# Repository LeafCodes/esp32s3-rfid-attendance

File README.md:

# 📇 ESP32-S3 RFID Attendance System

> **Sistem Presensi RFID Mandiri Berbasis IoT & Local-First Architecture**  
> Solusi presensi cerdas, hemat biaya, dan tahan kendala jaringan dengan integrasi *end-to-end*: **Custom PCB (KiCad) + Embedded C++ (ESP32-S3) + Modern Web Backend (FastAPI & SQLite)**.

---

## 📌 Latar Belakang & Masalah (*Problem Statement*)

Banyak institusi, sekolah, laboratorium, maupun startup menghadapi berbagai kendala dalam pencatatan kehadiran:
1. **Absensi Manual / Kertas**: Rawan manipulasi, rawan hilang, dan memakan waktu rekapitulasi yang tinggi.
2. **Mesin Biometrik (Fingerprint) Konvensional**: Sering gagal mengenali sidik jari yang kotor, berminyak, atau basah; menimbulkan antrean panjang di jam sibuk kerja/sekolah.
3. **Sistem Cloud Murni (*Pure Cloud-Dependent*)**: Jika koneksi internet ISP luar mati (*down*) atau latensi tinggi, seluruh proses absensi di kantor menjadi lumpuh dan karyawan tidak bisa tap kartu.
4. **Konfigurasi Jaringan yang Rumit**: Perangkat IoT tradisional sering mengharuskan pengaturan IP statis (*hardcoded*) pada firmware setiap kali berpindah router/jaringan.

---

## 💡 Solusi yang Ditawarkan (*The Engineering Solution*)

Proyek ini menghadirkan **arsitektur presensi lokal-mandiri (*Local-First & Offline-Resilient*)** yang andal dan mudah dioperasikan tanpa ketergantungan pada internet publik:

- 🛡️ **Offline-First & Auto-Synchronization**:  
  ESP32-S3 menyimpan daftar UID kartu aktif di memori EEPROM/Flash. Jika server PC atau jaringan mati, proses *tap* tetap berhasil dicatat ke dalam memori *offline buffer* lokal (LittleFS/RAM). Begitu server kembali online, data transaksi otomatis terkirim tanpa ada absensi yang hilang.
- 🔍 **Zero-Configuration Network (mDNS Discovery)**:  
  ESP32 secara cerdas mencari keberadaan server PC lokal di jaringan menggunakan protokol mDNS (`absensi-pc.local`). Pengguna tidak perlu mengubah kode atau mengatur IP statis saat berganti router.
- 📶 **WiFi Captive Portal (WiFiManager)**:  
  Konfigurasi SSID dan password dilakukan melalui halaman *web portal* saat ESP32 pertama kali dinyalakan atau saat jaringan berubah, tanpa perlu *flash* ulang firmware.
- ⏱️ **Double-Tap Debounce Protection**:  
  Backend FastAPI dilengkapi proteksi logika selisih waktu (<10 detik) untuk mencegah terjadinya duplikasi data saat karyawan menempelkan kartu berulang kali tanpa sengaja.
- 🔊 **Feedback Visual & Audio Real-Time**:  
  Respon instan kepada pengguna melalui LCD 16x2 I2C (nama karyawan dan status Masuk/Pulang), lampu status Dual LED, dan nada Buzzer spesifik (sukses vs ditolak).
- 📊 **Dashboard Interaktif & One-Click Excel Export**:  
  Admin dapat memantau log kehadiran secara *real-time*, mendaftarkan kartu baru via browser, dan mengekspor laporan lengkap ke format Microsoft Excel (`.xlsx`) siap olah.
- 🛠️ **Full-Stack Hardware-to-Software**:  
  Dirancang dari level sirkuit elektronik (desain skematik & PCB di KiCad), enclosure 3D print, hingga *full-stack software*.

---

## 🏗️ Arsitektur Sistem

Berikut adalah gambaran interaksi antara komponen perangkat keras dan aplikasi server:

```mermaid
flowchart LR
    subgraph EdgeDevice[" Perangkat Keras (Edge Device) "]
        RFID["RFID MFRC522\n(13.56MHz SPI)"] --> ESP["ESP32-S3 MCU\n(Dual-Core Xtensa)"]
        ESP --> LCD["LCD 16x2 I2C\n(Visual Info)"]
        ESP --> BUZZ["Buzzer & LED\n(Audio-Visual Status)"]
        ESP -. Buffer Luring .-> FS["Internal Flash / EEPROM\n(Offline Buffer & Card DB)"]
    end

    subgraph LocalNetwork[" Jaringan Area Lokal (WiFi / LAN) "]
        ESP -- "mDNS Service Discovery" --- MDNS["Resolusi: absensi-pc.local"]
        ESP -- "REST API (JSON / HTTP)" --- API["POST /api/attendance\nGET /api/cards"]
    end

    subgraph HostPC[" Server Lokal (PC / Mini PC) "]
        API --> FastAPI["FastAPI Backend Server\n(Uvicorn ASGI Engine)"]
        FastAPI --> SQLite[("SQLite Database\n(Cards, Logs, Settings)")]
        FastAPI --> WebUI["Web Dashboard & Reports\n(Jinja2 + Tailwind)"]
        FastAPI --> Excel["Export Engine\n(OpenPyXL .xlsx)"]
    end
```

> 📖 **Pelajari detail alur sistem & flowchart lengkap:** [docs/architecture_flowchart.md](docs/architecture_flowchart.md)

---

## ✨ Fitur-Fitur Utama

### 1. Sisi Firmware (ESP32-S3)
* **Dual-State Attendance Toggle**: Menentukan otomatis pergantian status `IN` (Masuk) atau `OUT` (Keluar).
* **NTP Clock Synchronization**: Jam internal tersinkronisasi otomatis via NTP (*Network Time Protocol*).
* **Smart Offline Buffer Recovery**: Mengirim antrean data luring secara otomatis begitu koneksi ke server pulih.
* **Modular Codebase**: Kode C++ tertata rapi dalam modul terpisah (`wifi_manager`, `rfid_handler`, `pc_client`, `offline_buffer`, `lcd_display`, `led_buzzer`).

### 2. Sisi Server & Web App (FastAPI)
* **Realtime Dashboard**: Menampilkan status kehadiran hari ini, waktu *tap*, serta rincian karyawan.
* **Interactive Enrollment Mode**: Pendaftaran kartu baru langsung dari web browser. Saat mode aktivasi menyala, kartu yang di-tap otomatis terdaftar ke profil pegawai baru.
* **Audit & Export Excel**: Unduh rekapitulasi presensi harian/bulanan dengan format rapi dan siap cetak.
* **Lightweight & High Performance**: Dibangun menggunakan FastAPI asynchronous dengan SQLite yang ringan dan mudah di-backup.

### 3. Sisi Hardware & PCB
* **Custom KiCad Design**: Skematik dan layout 2-layer siap cetak (*home-etching* toner transfer atau fabrikasi JLCPCB/PCBWay).
* **Decoupling Protection**: Dilengkapi kapasitor peredam *noise* pada jalur suplai daya MFRC522 dan ESP32.
* **Mounting Enclosure Ready**: Dimensi PCB 100×80 mm dirancang presisi untuk box/casing 3D print.

---

## 🧰 Kebutuhan Komponen (Hardware & Software)

### Komponen Elektronika
| Komponen | Spesifikasi / Tipe | Fungsi |
|---|---|---|
| **Microcontroller** | ESP32-S3 DevKitC-1 (WiFi + BLE) | Pemroses utama, konektivitas, buffer memori |
| **RFID Reader** | MFRC522 (13.56 MHz, SPI Interface) | Pembaca kartu RFID MIFARE |
| **Display** | LCD 16x2 Karakter dengan I2C Backpack | Penampil jam, sapaan nama, dan status |
| **Audio-Visual** | Active Buzzer 5V, LED Hijau, LED Merah | Indikator status sukses / ditolak |
| **Kartu/Tag** | MIFARE Classic 1K Card / Keyfob | Identitas pengguna / karyawan |
| **Catu Daya** | 5V DC (USB-C atau Adaptor 5V 1A) | Sumber daya sistem |

### Perangkat Lunak & Library
* **Firmware**: PlatformIO IDE, Arduino Framework for ESP32, LittleFS, ArduinoJson, MFRC522, LiquidCrystal_I2C, WiFiManager.
* **PC Backend**: Python 3.12+, FastAPI, Uvicorn, SQLAlchemy, SQLite, OpenPyXL, python-zeroconf.
* **EDA / PCB Tool**: KiCad 8.0+.

---

## 🚀 Panduan Memulai Cepat (*Quick Start*)

### 1. Flash Firmware ke ESP32-S3
Pastikan Anda telah memasang [PlatformIO Core / IDE](https://platformio.org/).

```bash
# Masuk ke direktori firmware
cd firmware

# Compile dan upload ke board ESP32-S3
pio run -t upload

# Buka Serial Monitor untuk memantau proses boot
pio device monitor
```

### 2. Menjalankan Server PC (FastAPI)
Buka terminal baru di komputer yang terhubung ke jaringan WiFi/LAN yang sama:

```bash
# Masuk ke direktori pc-app
cd pc-app

# Buat virtual environment (opsional namun disarankan)
python -m venv venv
# Windows:
venv\Scripts\activate
# Linux/macOS:
# source venv/bin/activate

# Install dependensi
pip install -r requirements.txt

# Jalankan server FastAPI
uvicorn app.main:app --host 0.0.0.0 --port 8000
```

### 3. Mengakses Web Dashboard
Buka browser web di komputer Anda lalu akses salah satu alamat berikut:
- 🌐 `http://localhost:8000`
- 🌐 `http://absensi-pc.local:8000`

---

## 📂 Struktur Repositori

```text
projek_absensi_rfid/
├── firmware/                  # Proyek Firmware PlatformIO (ESP32-S3)
│   ├── src/                   # Source code modular C++
│   │   ├── main.ino           # Logika utama (setup & loop)
│   │   ├── config.h           # Pemetaan pin hardware & parameter sistem
│   │   ├── rfid_handler.cpp   # Driver komunikasi MFRC522 (SPI)
│   │   ├── pc_client.cpp      # Klien HTTP REST API ke server PC
│   │   ├── mdns_client.cpp    # Resolusi nama server otomatis (mDNS)
│   │   ├── offline_buffer.cpp # Manajemen buffer antrean offline
│   │   ├── card_storage.cpp   # Cache UID kartu lokal pada Flash
│   │   └── ...
│   ├── include/               # Header deklarasi
│   └── platformio.ini         # Konfigurasi board & dependensi library
├── pc-app/                    # Aplikasi Server & Web (FastAPI)
│   ├── app/
│   │   ├── main.py            # Entry point FastAPI & zeroconf mDNS advertiser
│   │   ├── database.py        # Konfigurasi database SQLite & ORM engine
│   │   ├── models.py          # Model database: Card & AttendanceLog
│   │   ├── routes/            # REST API endpoints (cards, attendance, reports)
│   │   ├── services/          # Layanan mDNS broadcast & sync logic
│   │   ├── templates/         # UI Dashboard HTML (Jinja2)
│   │   └── static/            # Styling CSS & aset web
│   ├── tests/                 # Unit testing (Pytest)
│   └── requirements.txt       # Daftar dependensi Python
├── pcb/                       # Desain Perangkat Keras PCB (KiCad)
│   └── rfid-attendance/       # File skematik (.kicad_sch), PCB (.kicad_pcb),
│                              # dan berkas export SVG siap cetak
├── case/                      # File rancangan 3D enclosure / casing
├── docs/                      # Dokumentasi Teknis Mendalam
│   ├── architecture_flowchart.md # Diagram alur data & state machine lengkap
│   ├── setup-guide.md            # Panduan langkah demi langkah untuk teknisi & user
│   └── wiring.md                 # Diagram skematik pinout hardware & kelistrikan
└── README.md                  # Halaman utama dokumentasi proyek
```

---

## 📚 Panduan Dokumentasi Lengkap

Untuk eksplorasi teknis yang lebih komprehensif, silakan pelajari dokumen-dokumen berikut:
- 📐 [**Diagram Pengkabelan & Pinout (Wiring)**](docs/wiring.md) — Rincian jalur pin SPI/I2C/GPIO, level voltase, dan panduan kestabilan daya.
- ⚙️ [**Arsitektur & Flowchart Sistem**](docs/architecture_flowchart.md) — Alur logika state machine, penanganan offline buffer, dan kontrak API.
- 📖 [**Panduan Penggunaan & Troubleshooting**](docs/setup-guide.md) — Langkah operasional bagi pengguna non-teknis serta matriks penanganan masalah.
- 🔌 [**Dokumentasi Desain PCB & Fabrikasi**](pcb/rfid-attendance/README.md) — Spesifikasi PCB 2-layer, Bill of Materials (BOM), dan panduan cetak KiCad.

---

## 👨‍💻 Kontribusi & Lisensi

Proyek ini dirilis di bawah lisensi terbuka [MIT License](LICENSE). Bebas digunakan, dimodifikasi, dan dikembangkan untuk keperluan riset, edukasi, maupun implementasi komersial.

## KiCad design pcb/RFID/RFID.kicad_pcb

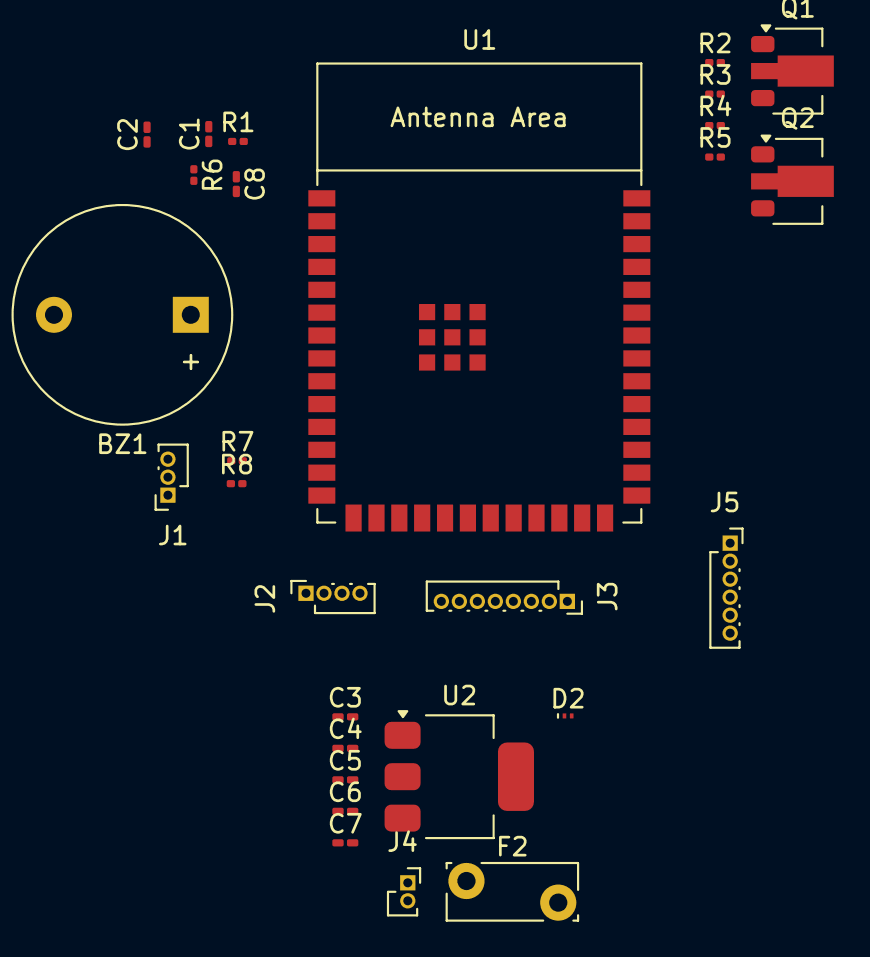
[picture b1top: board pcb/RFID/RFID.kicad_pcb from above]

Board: 2 copper layers, 28 parts (0 on the bottom side), 28 nets, no tracks yet.

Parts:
BZ1: Buzzer; Buzzer_12x9.5RM7.6
C1, C3, C4, C7: 10uF/25V(20%); C_0201_0603Metric_Pad0.64x0.40mm_HandSolder
C2: 0.1uF/25V(10%); C_0201_0603Metric_Pad0.64x0.40mm_HandSolder
C5, C6: 0.1uF/25V(20%); C_0201_0603Metric_Pad0.64x0.40mm_HandSolder
C8: 1uF/16V(10%); C_0201_0603Metric_Pad0.64x0.40mm_HandSolder
D2: LESD5D5.0CT1G; Nexperia_DSN0603-2_0.6x0.3mm_P0.4mm
F2: Polyfuse; Fuse_Bourns_MF-RG300
J1: LED_Socket; PinSocket_1x03_P1.00mm_Vertical
J2: LCD_Socket; PinSocket_1x04_P1.00mm_Vertical
J3: RFID_Socket; PinSocket_1x08_P1.00mm_Vertical
J4: Power_Socket; PinSocket_1x02_P1.00mm_Vertical
J5: Test_Point; PinSocket_1x06_P1.00mm_Vertical
Q1, Q2: BCV29; SOT-89-3
R1, R4, R5: 0(1%); R_0201_0603Metric
R2, R3, R6: 10k(1%); R_0201_0603Metric
R7, R8: 220; R_0201_0603Metric
U1: ESP32-S3-WROOM-1
U2: AMS1117; SOT-223-3_TabPin2

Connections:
/Power_management_n_Protection/VBUS: C3.1, C4.1, C5.1, D2.2 (A2), F2.2, U2.3 (VI)
/Power_management_n_Protection/VCC_3V3: C6.1, C7.1, U2.2 (VO)
/System block/Buzzer: BZ1.1 (+), U1.8 (GPIO15/U0RTS/ADC2_CH4/XTAL_32K_P)
/System block/CHIP_PU: C8.1, R4.2, R6.2, U1.3 (EN)
/System block/DTR: J5.6, Q2.3 (E), R2.1
/System block/ESP_3V3: J3.1, R1.2, R6.1, U1.2 (3V3)
/System block/GPIO0: R5.2, U1.27 (GPIO0/BOOT)
/System block/LED_HIJAU: R7.2, U1.9 (GPIO16/U0CTS/ADC2_CH5/XTAL_32K_N)
/System block/LED_MERAH: R8.2, U1.10 (GPIO17/U1TXD/ADC2_CH6)
/System block/MISO: J3.5, U1.21 (GPIO13/TOUCH13/ADC2_CH2/FSPIQ/FSPIIO7/S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)
/System block/MOSI: J3.6, U1.19 (GPIO11/TOUCH11/ADC2_CH0/FSPID/FSPIIO5/S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)
/System block/RST: J3.2, U1.22 (GPIO14/TOUCH14/ADC2_CH3/FSPIWP/FSPIDQS/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)
/System block/RTS: J5.2, Q1.3 (E), R3.1
/System block/SCK: J3.7, U1.20 (GPIO12/TOUCH12/ADC2_CH1/FSPICLK/FSPIIO6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)
/System block/SCL_LCD: J2.4, U1.17 (GPIO9/TOUCH9/ADC1_CH8/FSPIHD/SUBSPIHD)
/System block/SDA: J3.8, U1.18 (GPIO10/TOUCH10/ADC1_CH9/FSPICS0/FSPIIO4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)
/System block/SDA_LCD: J2.3, U1.12 (GPIO8/TOUCH8/ADC1_CH7/SUBSPICS1)
/System block/U0RXD: J5.5, U1.36 (U0RXD/GPIO44/CLK_OUT2)
/System block/U0TXD: J5.4, U1.37 (U0TXD/GPIO43/CLK_OUT1)
/System block/VCC_3V3: C1.1, C2.1, R1.1
GND: BZ1.2 (-), C1.2, C2.2, C3.2, C4.2, C5.2, C6.2, C7.2, C8.2, D2.1 (A1), J1.1, J2.1, J3.3, J4.2, J5.1, U1.1 (GND), U1.40 (GND), U1.41 (GND), U2.1 (ADJ)
unnamed: J1.2, R8.1
unnamed: J1.3, R7.1
unnamed: F2.1, J4.1
unnamed: Q1.1 (B), R2.2
unnamed: Q1.2 (C), R4.1
unnamed: Q2.1 (B), R3.2
unnamed: Q2.2 (C), R5.1

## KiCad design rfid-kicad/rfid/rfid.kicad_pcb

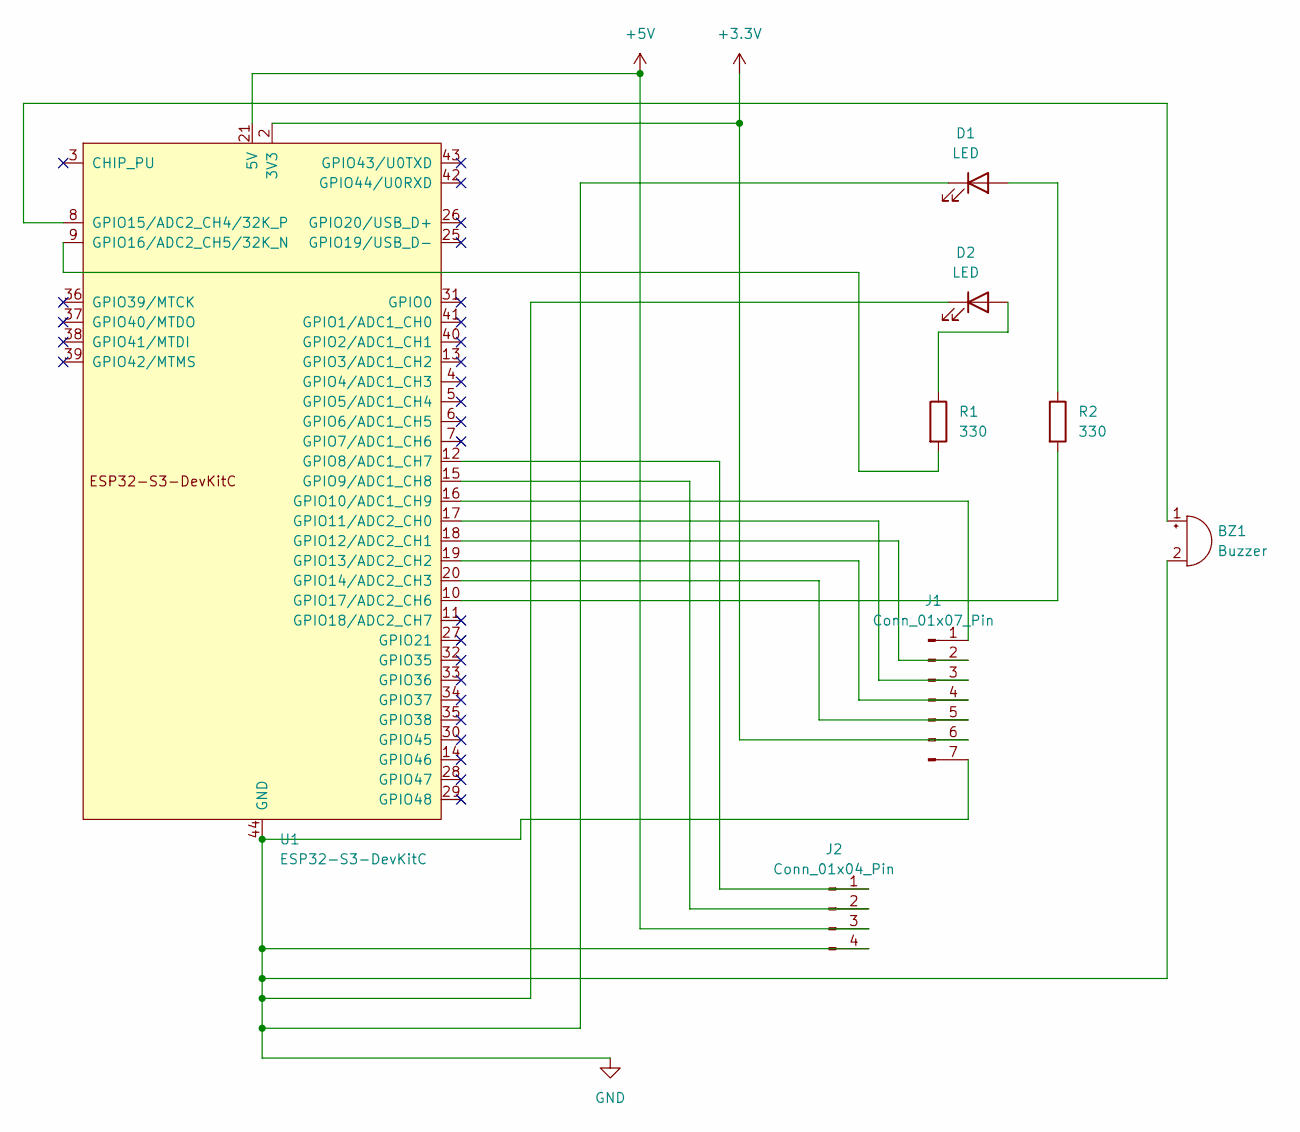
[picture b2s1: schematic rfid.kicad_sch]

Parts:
BZ1: Buzzer; Buzzer_12x9.5RM7.6
D1, D2: LED; LED_D1.8mm_W3.3mm_H2.4mm
J1: Conn_01x07_Pin; PinHeader_1x07_P1.00mm_Vertical
J2: Conn_01x04_Pin; PinHeader_1x04_P1.00mm_Vertical
R1, R2: 330; R_Axial_DIN0204_L3.6mm_D1.6mm_P1.90mm_Vertical
U1: ESP32-S3-DevKitC

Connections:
+3.3V: J1.6, U1.1 (3V3), U1.2 (3V3)
+5V: J2.3, U1.21 (5V)
GND: BZ1.2 (-), D1.1 (K), D2.1 (K), J1.7, J2.4, U1.22 (GND), U1.23 (GND), U1.24 (GND), U1.44 (GND)
unnamed: BZ1.1 (+), U1.8 (GPIO15/ADC2_CH4/32K_P)
unnamed: D1.2 (A), R2.1
unnamed: D2.2 (A), R1.1
unnamed: J1.1, U1.16 (GPIO10/ADC1_CH9)
unnamed: J1.2, U1.18 (GPIO12/ADC2_CH1)
unnamed: J1.3, U1.17 (GPIO11/ADC2_CH0)
unnamed: J1.4, U1.19 (GPIO13/ADC2_CH2)
unnamed: J1.5, U1.20 (GPIO14/ADC2_CH3)
unnamed: J2.1, U1.12 (GPIO8/ADC1_CH7)
unnamed: J2.2, U1.15 (GPIO9/ADC1_CH8)
unnamed: R1.2, U1.9 (GPIO16/ADC2_CH5/32K_N)
unnamed: R2.2, U1.10 (GPIO17/ADC2_CH6)

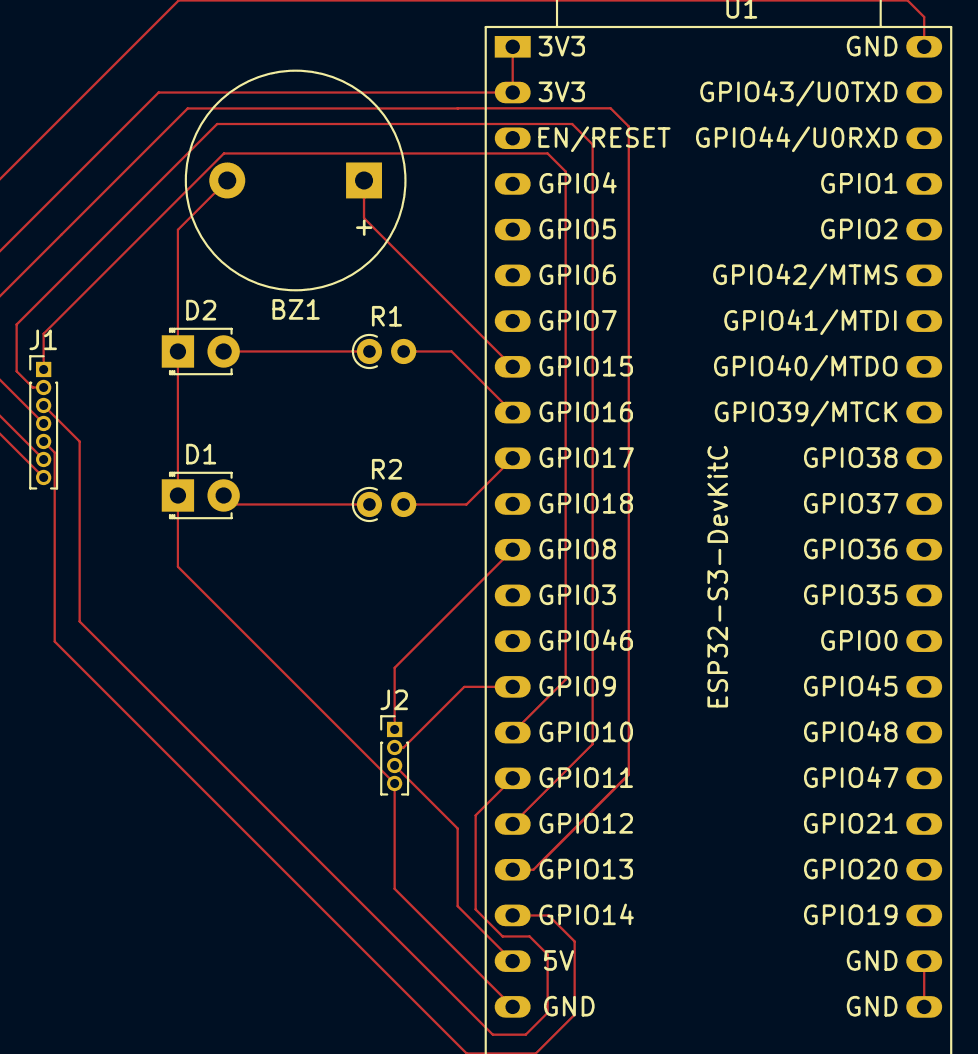
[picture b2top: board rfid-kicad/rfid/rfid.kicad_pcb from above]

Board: 2 copper layers, 8 parts (0 on the bottom side), 15 nets.

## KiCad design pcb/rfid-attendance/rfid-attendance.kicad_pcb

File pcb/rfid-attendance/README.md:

# 🛠️ Desain Perangkat Keras & Panduan Manufaktur PCB

Direktori ini berisi seluruh berkas desain perangkat keras (*hardware design files*) sistem presensi RFID berbasis mikrokontroler **ESP32-S3** yang dirancang menggunakan perangkat lunak **KiCad 8.0**.

---

## 📑 Daftar Isi
1. [Struktur & Deskripsi Berkas](#1-struktur--deskripsi-berkas)
2. [Spesifikasi Teknis Papan PCB](#2-spesifikasi-teknis-papan-pcb)
3. [Daftar Komponen Lengkap (Bill of Materials / BOM)](#3-daftar-komponen-lengkap-bill-of-materials--bom)
4. [Opsi Fabrikasi Papan PCB](#4-opsi-fabrikasi-papan-pcb)
   - [Opsi A: Fabrikasi Profesional Industri (JLCPCB / PCBWay)](#opsi-a-fabrikasi-profesional-industri-jlcpcb--pcbway)
   - [Opsi B: Pembuatan Mandiri / DIY (Metode Toner Transfer & Etsa)](#opsi-b-pembuatan-mandiri--diy-metode-toner-transfer--etsa)
5. [Prinsip Desain & Rekayasa Sirkuit (Design Considerations)](#5-prinsip-desain--rekayasa-sirkuit-design-considerations)

---

## 1. Struktur & Deskripsi Berkas

| Berkas | Jenis / Format | Deskripsi & Kegunaan |
|---|---|---|
| `rfid-attendance.kicad_pro` | Project KiCad | Berkas utama proyek KiCad 8.0 |
| `rfid-attendance.kicad_sch` | Skematik Elektronika | Diagram skema rangkaian terpadu sistem |
| `rfid-attendance.kicad_pcb` | Layout Jalur PCB | Penataan komponen dan jalur tembaga (*routing*) |
| `rfid-attendance-schematic.svg` | Gambar Vektor SVG | **Skematik siap cetak** — buka langsung di browser, tekan `Ctrl + P` |
| `rfid-attendance-pcb.svg` | Gambar Vektor SVG | **Jalur PCB skala 1:1 siap cetak** untuk etsa mandiri |
| `sym-lib-table` & `fp-lib-table` | Tabel Library | Konfigurasi pustaka simbol dan footprint KiCad |

---

## 2. Spesifikasi Teknis Papan PCB

Papan dirancang sesuai standar fabrikasi industri 2-layer (*double-sided*) yang ekonomis dan mudah diproduksi massal:

| Parameter Desain | Nilai Spesifikasi | Keterangan |
|---|---|---|
| **Dimensi Fisik** | 100 mm × 80 mm | Pas dengan ukuran box casing 3D print |
| **Jumlah Lapisan (*Layers*)** | 2 Layer (Top & Bottom) | Distribusi sinyal di Top, Ground plane di Bottom |
| **Material Substrat** | FR-4 Standard | Tahan panas dan memiliki isolasi tinggi |
| **Ketebalan Papan** | 1.6 mm | Standar ketebalan mekanikal yang kokoh |
| **Ketebalan Tembaga (*Copper*)** | 1 oz (35 µm) | Kapasitas arus memadai untuk modul RF |
| **Solder Mask** | Hijau / Matte Black | Melindungi jalur tembaga dari oksidasi |
| **Silkscreen** | Putih (White) | Label teks indikasi pin dan orientasi komponen |
| **Lebar Jalur Sinyal (*Trace*)** | Min. 0.25 mm (10 mil) | Untuk jalur komunikasi SPI dan I2C |
| **Lebar Jalur Daya (*Power*)** | Min. 0.60 mm – 1.0 mm | Menjamin drop tegangan minimal pada jalur 5V/3.3V |
| **Jarak Antar Jalur (*Clearance*)** | Min. 0.20 mm (8 mil) | Menghindari risiko korsleting pada proses etsa |
| **Lubang Baut (*Mounting Hole*)** | 4× Lubang M3 (Ø 3.2 mm) | Di keempat sudut untuk penguncian ke enclosure |

---

## 3. Daftar Komponen Lengkap (Bill of Materials / BOM)

Komponen dirancang dominan menggunakan tipe **Through-Hole Technology (THT)** agar sangat mudah disolder secara manual oleh teknisi, mahasiswa, maupun hobiis:

| No | Nama Komponen | Referensi Skematik | Qty | Tipe Paket (Package) | Keterangan Tambahan |
|---|---|---|---|---|---|
| 1 | **ESP32-S3 DevKitC-1** | U1 | 1 | Modul Soket 2×15 Pin (2.54mm) | Disarankan menggunakan female header |
| 2 | **Modul RFID MFRC522** | U2 | 1 | Modul Soket 1×8 Pin (2.54mm) | Dipasang tegak/sejajar pembaca kartu |
| 3 | **Modul LCD 16x2 I2C** | LCD1 | 1 | Header 1×4 Pin (2.54mm) | Koneksi VCC, GND, SDA, SCL |
| 4 | **Buzzer Aktif 5V** | BZ1 | 1 | THT Pitch 7.6mm | Indikator suara |
| 5 | **LED Indikator Hijau (5mm)** | D1 | 1 | Radial THT 5mm | Status Berhasil / Masuk |
| 6 | **LED Indikator Merah (5mm)** | D2 | 1 | Radial THT 5mm | Status Gagal / Error |
| 7 | **Resistor 220Ω 1/4W** | R1, R2, R3 | 3 | Aksial THT | Pembatas arus LED & Buzzer |
| 8 | **Resistor 4.7kΩ 1/4W** | R4, R5 | 2 | Aksial THT | Resistor Pull-up eksternal I2C (Opsional) |
| 9 | **Kapasitor Elektrolit 100µF 16V** | C1, C2 | 2 | Radial THT | Decoupling filter pada rel 5V dan 3.3V |
| 10 | **Pin Header Male/Female 2.54mm** | J1 - J4 | 4 | Strip Header | Konektor modular |

---

## 4. Opsi Fabrikasi Papan PCB

### Opsi A: Fabrikasi Profesional Industri (JLCPCB / PCBWay)
Metode ini menghasilkan papan dengan kualitas pabrikan lengkap dengan *through-hole plating*, *solder mask*, dan *silkscreen*:

1. Buka berkas `rfid-attendance.kicad_pcb` di **KiCad PCB Editor**.
2. Masuk ke menu **File → Plot**.
3. Centang layer yang diperlukan:
   - `F.Cu` (Top Copper)
   - `B.Cu` (Bottom Copper)
   - `F.Paste` & `B.Paste` (Jika menggunakan SMD stencil)
   - `F.Silkscreen` & `B.Silkscreen`
   - `F.Mask` & `B.Mask`
   - `Edge.Cuts` (Garis batas tepi papan PCB)
4. Klik tombol **Generate Drill Files (.drl)**.
5. Kumpulkan semua berkas `.gbr` dan `.drl` ke dalam satu berkas `.zip`.
6. Unggah berkas `.zip` ke layanan fabrikasi (misalnya [JLCPCB](https://jlcpcb.com) atau [PCBWay](https://www.pcbway.com)).
7. Pilih spesifikasi: `2 Layers`, `100x80mm`, `Thickness 1.6mm`, warna solder mask sesuai selera.

---

### Opsi B: Pembuatan Mandiri / DIY (Metode Toner Transfer & Etsa)
Jika Anda ingin mencetak PCB sendiri di laboratorium atau bengkel kerja:

1. Buka berkas **`rfid-attendance-pcb.svg`** menggunakan browser web modern (Google Chrome / Mozilla Firefox / MS Edge).
2. Tekan kombinasi tombol **`Ctrl + P`** untuk membuka dialog pencetakan.
3. Atur konfigurasi printer:
   - **Ukuran Kertas**: A4
   - **Skala (*Scale*)**: Wajib **100% (Actual Size)** — *Jangan pilih "Fit to Page" agar dimensi kaki IC tidak meleset*.
4. Cetak ke kertas kalkir / kertas transfer (*glossy paper*) menggunakan **Printer Laser (Toner Hitam)**.
5. Tempelkan toner ke papan tembaga polos menggunakan setrika panas (*heat transfer*), lalu larutkan tembaga berlebih menggunakan cairan ferric chloride ($FeCl_3$) atau H2O2 + HCl.
6. Bor lubang pin komponen menggunakan mata bor mini berukuran 0.8 mm dan 1.0 mm.

---

## 5. Prinsip Desain & Rekayasa Sirkuit (Design Considerations)

1. **Modularitas Komponen (Soket Female Header):**  
   Papan dirancang menggunakan header modular sehingga modul mikrokontroler ESP32-S3 dan MFRC522 dapat dilepas-pasang dengan mudah tanpa perlu menyolder ulang saat proses servis atau pergantian komponen.
2. **Ground Plane (Copper Pour):**  
   Seluruh area kosong pada lapisan bawah (*Bottom Layer*) dihubungkan ke sinyal GND (*Ground Pour*). Hal ini berfungsi sebagai pelindung interferensi elektromagnetik (*EMI shielding*) serta meminimalkan impedansi jalur balik arus daya.
3. **Peredaman Lonjakan Arus (Decoupling Capacitor):**  
   Kapasitor 100µF diposisikan sedekat mungkin dengan pin input daya modul RFID untuk menjaga kestabilan voltase saat medan antena 13.56 MHz memancarkan daya ke kartu transponder.

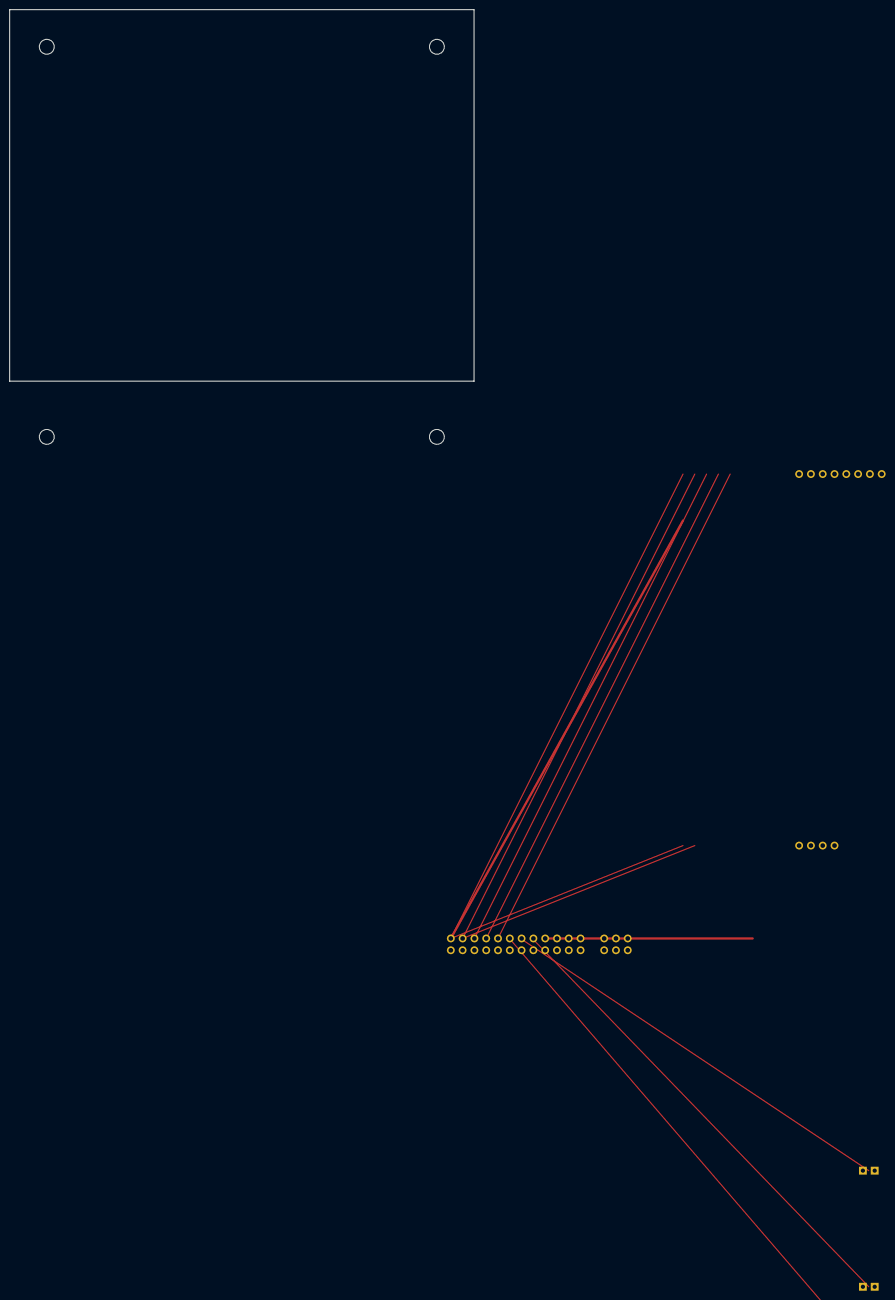
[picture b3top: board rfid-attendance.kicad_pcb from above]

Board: 2 copper layers, 100.0 x 80.0 mm, 9 parts (0 on the bottom side), 12 nets.

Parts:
D1: LED_HIJAU; LED_D5.0mm
D2: LED_MERAH; LED_D5.0mm
H1, H2, H3, H4: MountingHole_3.2mm_M3
J1: ESP32-S3_DevKitC-1; PinHeader_2x15_P2.54mm_Vertical
J2: MFRC522_RFID; PinHeader_1x08_P2.54mm_Vertical
J3: LCD_16x2_I2C; PinHeader_1x04_P2.54mm_Vertical

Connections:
+3.3V: J1.1, J2.5
+5V: J1.14, J3.2
GND: D1.2, D2.2, J1.2, J1.15, J1.30, J2.6, J3.1
I2C_SCL: J1.4, J3.4
I2C_SDA: J1.3, J3.3
LED_HIJAU: D1.1, J1.11
LED_MERAH: D2.1, J1.12
SPI_MISO: J1.8, J2.4
SPI_MOSI: J1.6, J2.3
SPI_RST: J1.9, J2.8
SPI_SCK: J1.7, J2.2
SPI_SS: J1.5, J2.1

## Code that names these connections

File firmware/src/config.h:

#ifndef CONFIG_H
#define CONFIG_H

// RFID MFRC522 pin (SPI - ESP32-S3)
#define SPI_SCK   12
#define SPI_MISO  13
#define SPI_MOSI  11
#define RFID_SS   10
#define RFID_RST  14

// I2C LCD (ESP32-S3)
#define LCD_SDA   8
#define LCD_SCL   9
#define LCD_ADDR  0x3F
#define LCD_COLS  16
#define LCD_ROWS  2

// Buzzer & LED (ESP32-S3)
#define BUZZER_PIN  15
#define LED_GREEN   16
#define LED_RED     17

// NTP
#define NTP_SERVER     "pool.ntp.org"
#define GMT_OFFSET     7  // WIB (UTC+7)

// PC Server
#define PC_PORT        8000
#define MDNS_SERVICE   "attendance"
#define API_KEY        "absensi_secret_key_2026"

// EEPROM
#define EEPROM_SIZE    4096
#define MAX_CARDS      90

// LittleFS
#define BUFFER_DIR     "/buffer"
#define INDEX_FILE     "/buffer/index.json"

// Debounce
#define SCAN_COOLDOWN  3000  // ms

#endif

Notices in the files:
README.md:
License: MIT
